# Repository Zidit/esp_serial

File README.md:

ESP8266 SERIAL ADAPTER
======================
This is basic board for connecting esp8266 to usb/serial adapter. It works also with [esptool](https://github.com/pfalcon/esptool) programming software.

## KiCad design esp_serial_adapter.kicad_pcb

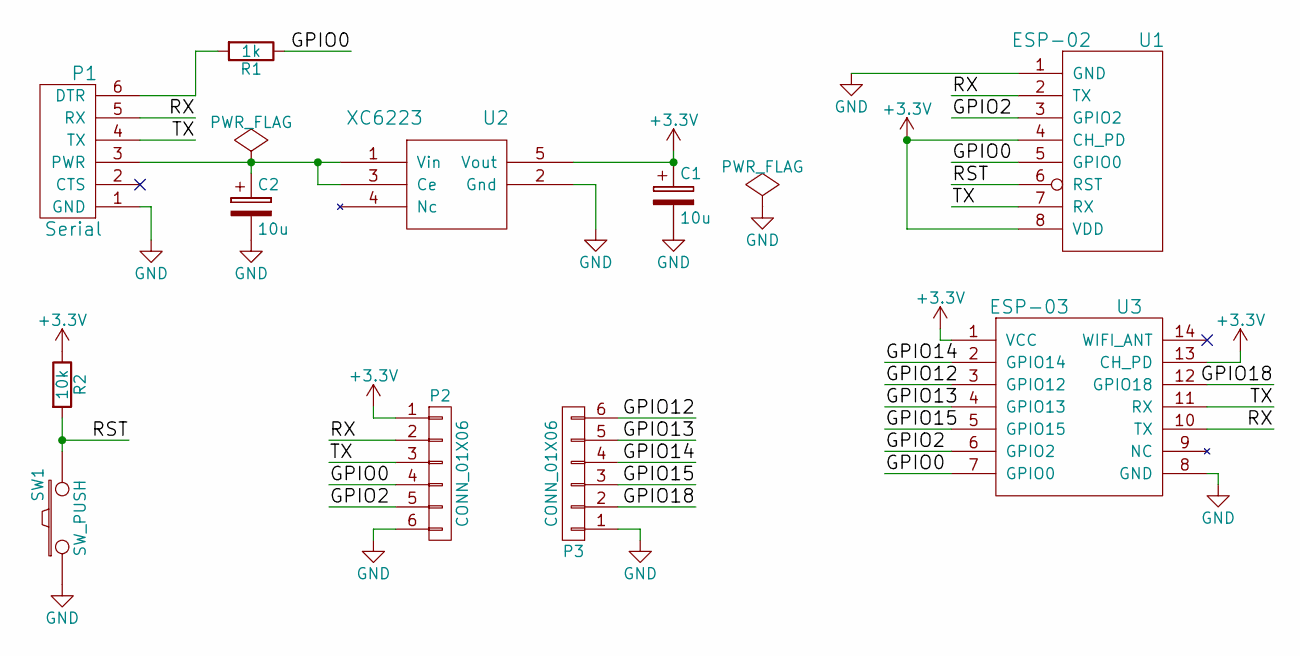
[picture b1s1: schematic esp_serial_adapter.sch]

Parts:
C1, C2: 10u; TantalC_SizeB_EIA-3528_Wave
P1: Serial; Pin_Header_Straight_1x06
P2, P3: CONN_01X06; Pin_Header_Straight_1x06
R1: 1k; R_0603_HandSoldering
R2: 10k; R_0603_HandSoldering
SW1: SW_PUSH; SW_SPST_PTS645
U1: ESP-02; Pin_Header_Straight_2x04
U2: XC6223; SOT-23-5
U3: ESP-03

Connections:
+3V3: C1.1, P2.1, R2.1, U1.4 (CH_PD), U1.8 (VDD), U2.5 (Vout), U3.1 (VCC), U3.13 (CH_PD)
/GPIO0: P2.4, R1.1, U1.5 (GPIO0), U3.7 (GPIO0)
/GPIO2: P2.5, U1.3 (GPIO2), U3.6 (GPIO2)
/GPIO12: P3.6, U3.3 (GPIO12)
/GPIO13: P3.5, U3.4 (GPIO13)
/GPIO14: P3.4, U3.2 (GPIO14)
/GPIO15: P3.3, U3.5 (GPIO15)
/GPIO18: P3.2, U3.12 (GPIO18)
/RST: R2.2, SW1.2, U1.6 (RST)
/RX: P1.5 (RX), P2.2, U1.2 (TX), U3.10 (TX)
/TX: P1.4 (TX), P2.3, U1.7 (RX), U3.11 (RX)
GND: C1.2, C2.2, P1.1 (GND), P2.6, P3.1, SW1.1, U1.1 (GND), U2.2 (Gnd), U3.8 (GND)
unnamed: C2.1, P1.3 (PWR), U2.1 (Vin), U2.3 (Ce)
unnamed: P1.6 (DTR), R1.2

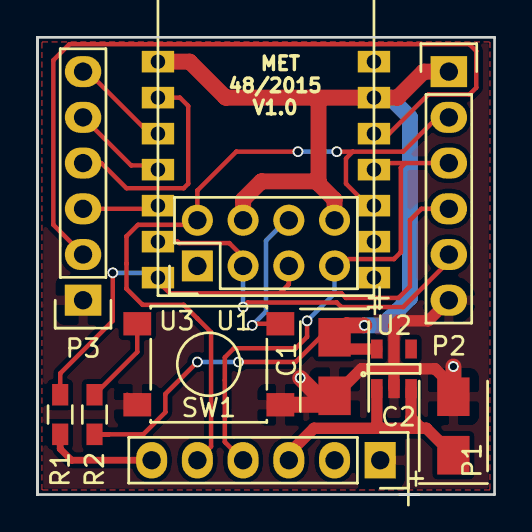
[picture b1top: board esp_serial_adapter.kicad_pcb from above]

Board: 2 copper layers, 25.4 x 25.4 mm, 11 parts (0 on the bottom side), 14 nets.
